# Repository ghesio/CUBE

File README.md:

# CUBE

## What it is

The CUBE is an IOT device with programmable 6 axis gyroscope/accelerometer, programmable LED lights, IR sensor and Bluetooth Low Energy connection.

It's based on Arduino/Genuino 101, featuring a 3D printed and laser cut shell custom designed.

The challenge of this project was to build a device with programmable functions, capable of working on different contexts, aimed at developers who can develop their own use and improvements for the CUBE.

The main idea is to use this as a music controller: based on gyroscope movements and native applications API, you can control the music you are playing; you can change the song you are listening to by rotating it, you can shuffle the music by shaking it.

It’s possible to use it as a volume controller, like a potentiometer: by rotating it with one side laying on the desk, you can increase or decrease music volume.

It will have an infrared sensor to play/stop music by swiping the hand over it.

## Features

- BLE enable
- Battery powered
- 6-Axis gyroscope
- Distance measure
- 4 LEDs acting as output/information

## Functions:

- Able to recognize rotations (clockwise and counterclockwise only, right now)
- Able to recognize swipes of the hand
- Able to recognize the heading of the cube: you can get the angle of the CUBE
- Able to recognize on which side the CUBE is on

### BOM  

- 1 x Arduino/Genuino 101
- 4 x Neopixel LEDs
- 1 x IR emitter
- 1 x IR receiver
- 1 x Switch
- 1 x 9V battery
- Lasercut and printed parts (with the material you prefer)
- Hot glue
- 20 M3 nuts
- 20 M3 1 cm screws
- Vinyl for stickers

On this repo there are also eagle files for doing an (optional) breakout board for building this project.

## BLE Reference

### Mode control, read/write
*uuid: 988dbab9-a657-45fe-80ef-9f9bed761947, read/write*

This service let choose in which mode you want to use the CUBE

0: Stand-by

1: rotation recognition

2: Swipe recognition

3: Potentiometer mode

4: Face recognition

### Rotations, read/write/notify
*uuid: 988dbab9-a657-45fe-80ef-9f9bed761948, read/write/notify*

This service keeps tracks of the rotations.
When the value is 0, no rotation happened, when it's 1 a left rotation happened, when it's 2 a right rotation happened.
Agter every rotation is necessary to write 0 before reading another.

NOTE: rotations are recognized only clockwise/counterclockwise in the direction indicated in the CUBE.

### LED, read/write
*uuid: 988dbab9-a657-45fe-80ef-9f9bed761949, read/write*

With this service it's possible to control the LEDs.

Write as value a 16-byte char array, where (the number reported here are the index of the array):
- 0: led number (possible value 3,5,6,9)
- 1-3 red component of the color (these 3 bytes represents a number between 0 and 255)
- 4-6 green component of the color (these 3 bytes represents a number between 0 and 255)
- 7-9 blue component of the color (these 3 bytes represents a number between 0 and 255)
- 10-12 white component of the color (these 3 bytes represents a number between 0 and 255)
- 13-15 brigthness (these 3 bytes represents a number between 0 and 255)

Examples:
- 3255000000000050: led #3 turned on, red with brigthness 50
- 3000000000000000: led #3 turned off
- 5000255000000255: led #5 turned on, green with max brigthness

### Swipe, read/write/notify
*uuid: 988dbab9-a657-45fe-80ef-9f9bed761950*

This service keeps track of the swipes.
When the value becomes 1, a swipe happened.
It's needed then to write 0 again in the charachteristic.

### Potenziometro, read/notify
*uuid: 988dbab9-a657-45fe-80ef-9f9bed761951*

This service advertise the CUBE angle.
It's only necessary to read the charachteristic value.
Note: there is a drifting in the PID controlling the gyroscope of about 2 degrees every half and hour.

### Riconoscimento della faccia

Based on which face the CUBE lies on, it's possible to set a different function.
Note: the active face is always the one where you can see the sticker with the number
Note: To use this mode is necessary to do a rotation before in mode 1.

### Final note

If the CUBE starts working random

## Future works / full develompent

My work on this, due to time available is over.

You can get the full story behind the develompent here: https://goo.gl/xEmkgw

Future improvements:
- Shake recognition
- Develop a real application as music controller
- Recognize all rotations

## Presentation video

https://vimeo.com/226481945

## Credits

A special thanks goes to Patrizia Marti and Matteo Sirizzotti.
A special thanks also goes to Elis Taflaj for filming and editing this video.

## License

Copyright (c) 2017 Nicola Giannelli

Permission is hereby granted, free of charge, to any person obtaining a copy of this software and associated documentation files (the "Software"), to deal in the Software without restriction, including without limitation the rights to use, copy, modify, merge, publish, distribute, sublicense, and/or sell copies of the Software, and to permit persons to whom the Software is furnished to do so, subject to the following conditions:
The above copyright notice and this permission notice shall be included in all copies or substantial portions of the Software.
THE SOFTWARE IS PROVIDED "AS IS", WITHOUT WARRANTY OF ANY KIND, EXPRESS OR IMPLIED, INCLUDING BUT NOT LIMITED TO THE WARRANTIES OF MERCHANTABILITY, FITNESS FOR A PARTICULAR PURPOSE AND NONINFRINGEMENT. IN NO EVENT SHALL THE AUTHORS OR COPYRIGHT HOLDERS BE LIABLE FOR ANY CLAIM, DAMAGES OR OTHER LIABILITY, WHETHER IN AN ACTION OF CONTRACT, TORT OR OTHERWISE, ARISING FROM, OUT OF OR IN CONNECTION WITH THE SOFTWARE OR THE USE OR OTHER DEALINGS IN THE SOFTWARE.

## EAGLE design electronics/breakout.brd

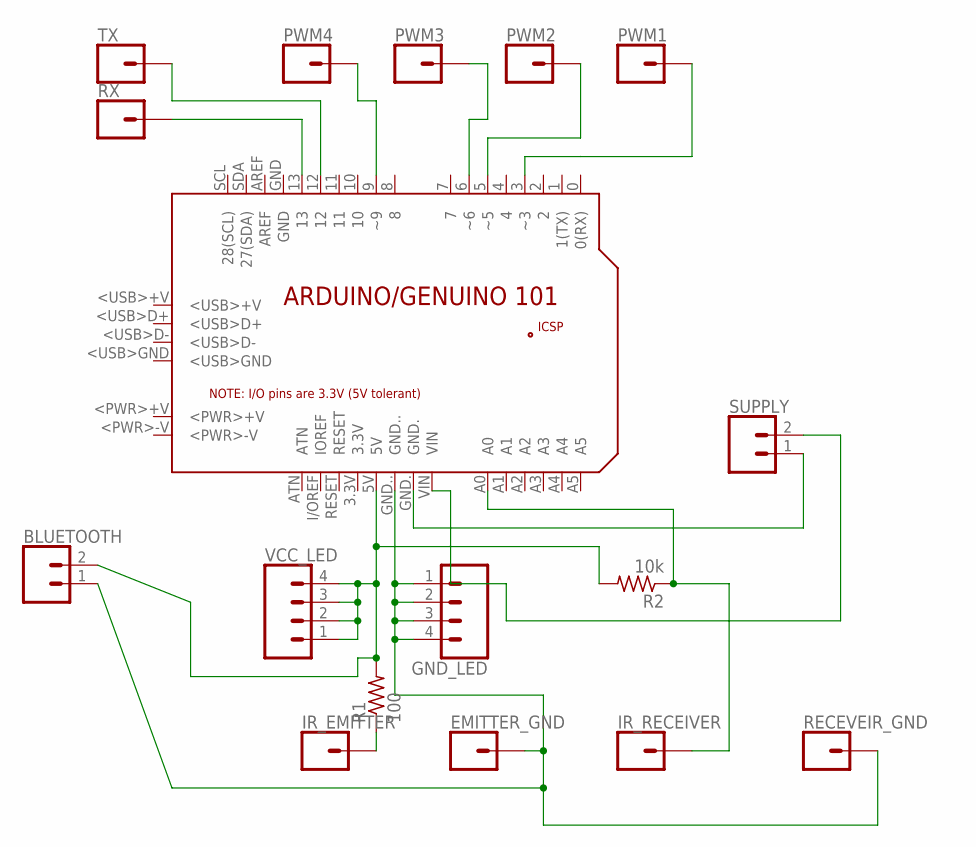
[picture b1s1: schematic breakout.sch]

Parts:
BLUETOOTH: CONN_02; 1X02
EMITTER_GND: CONN_01; 1X01
GND_LED: CONN_04; 1X04
IR_EMITTER: CONN_01; 1X01
IR_RECEIVER: CONN_01; 1X01
PCB1: ARDUINO_101
PWM1, PWM2, PWM3, PWM4: CONN_01; 1X01
R1: 100; R1206
R2: 10k; R1206
RECEVEIR_GND: CONN_01; 1X01
RX: CONN_01; 1X01
SUPPLY: CONN_02; 1X02
TX: CONN_01; 1X01
VCC_LED: CONN_04; 1X04

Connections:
unnamed: BLUETOOTH.2, PCB1.5V, R1.2, R2.2, VCC_LED.1, VCC_LED.2, VCC_LED.3, VCC_LED.4
unnamed: PCB1.GND., SUPPLY.1
unnamed: PCB1.3 (~3), PWM1.1
unnamed: PCB1.9 (~9), PWM4.1
unnamed: PCB1.5 (~5), PWM2.1
unnamed: PCB1.6 (~6), PWM3.1
unnamed: PCB1.VIN, SUPPLY.2
unnamed: IR_EMITTER.1, R1.1
unnamed: PCB1.13, RX.1
unnamed: IR_RECEIVER.1, PCB1.A0, R2.1
unnamed: PCB1.12, TX.1
unnamed: BLUETOOTH.1, EMITTER_GND.1, GND_LED.1, GND_LED.2, GND_LED.3, GND_LED.4, PCB1.GND.., RECEVEIR_GND.1

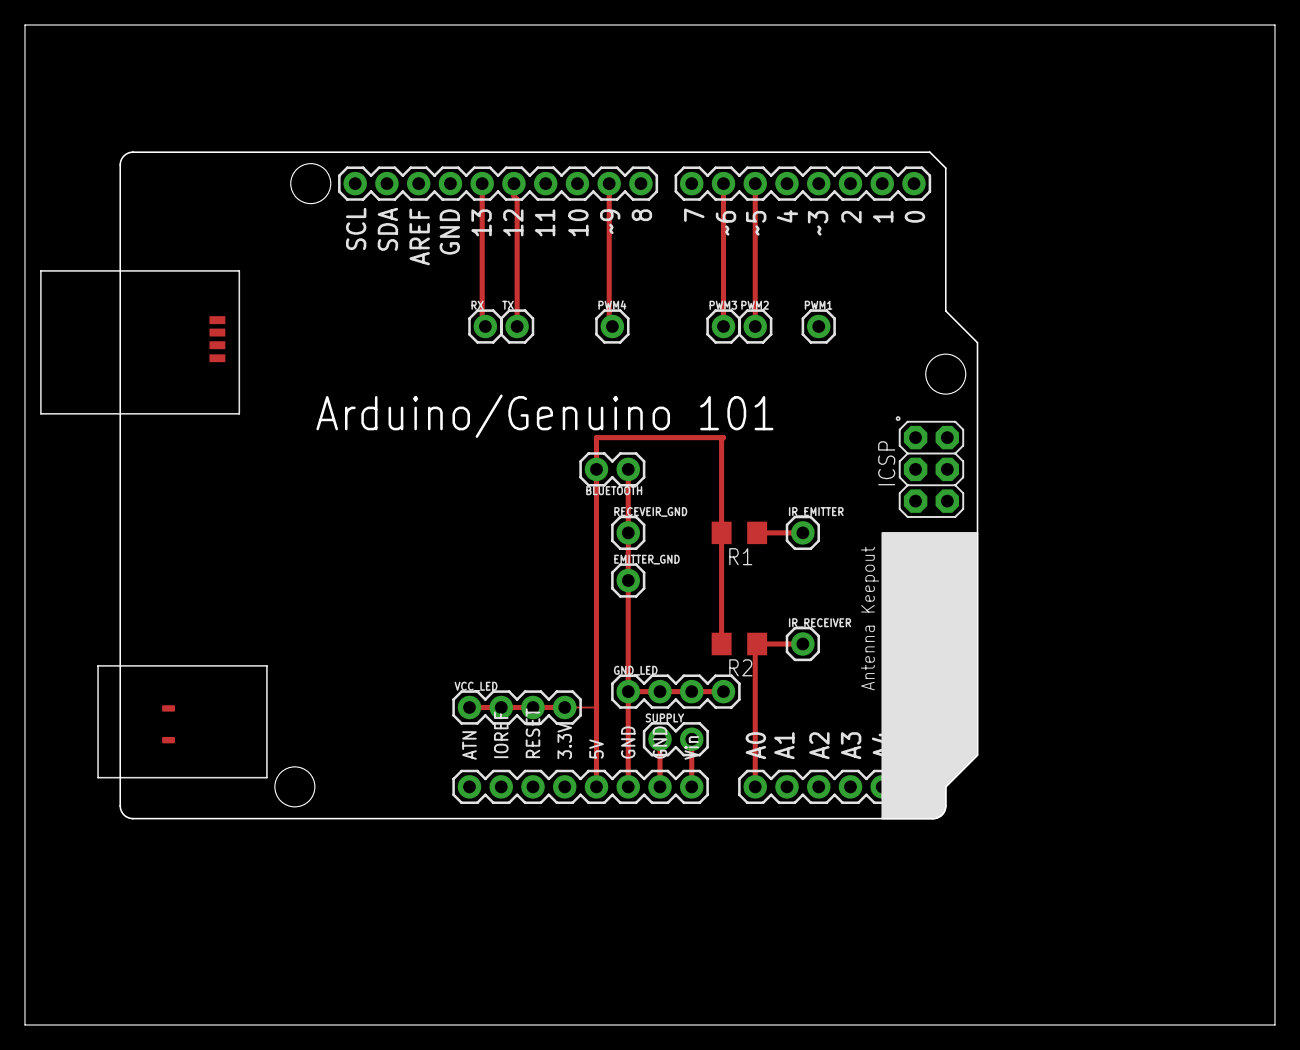
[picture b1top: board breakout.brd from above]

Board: 2 copper layers, 99.9 x 79.9 mm, 17 parts (0 on the bottom side), 12 nets.

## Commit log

2017-07-22 ReadMe
    Written readme
2017-07-22 Added files
    Fixed ReadMe. Added Files

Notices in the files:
parts and their libraries:
03_SparkFun-Connectors: Licensing: Creative Commons ShareAlike 4.0 International - https://creativecommons.org/licenses/by-sa/4.0
